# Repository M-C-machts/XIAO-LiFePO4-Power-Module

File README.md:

# XIAO LiFePO4 Module (Charging + 3.3V Regulator)

Small power-management PCB for running an ESP32 (or other 3.3V devices) from a single **LiFePO4** cell.

This board provides:
- **LiFePO4 charging** from ~5V input
- Proper handling of **charge + discharge**
- A **stable 3.3V output**
- **Battery voltage sense** output via a resistor divider (for ADC monitoring)

## Form factor / compatibility

This module matches the **Seeed Studio XIAO** form factor (approx. 21 x 17.5 mm) and is intended to be:
- soldered directly onto a **Seeed Studio XIAO ESP32C3** (castellated-module style), or
- used as a small **daughter board** on a larger PCB.

## Connections

- **Battery**: JST SH connector (LiFePO4 cell)
- **Charge input**: ~5V
- **Output**: regulated 3.3V
- **VBAT_SENSE**: divided battery-voltage output (connect to an ADC pin)

> Pin names / exact pinout depends on the PCB revision. See the schematic/PCB files in this repo.

## Typical use cases

- Battery-powered ESP32 sensor nodes
- Small portable projects using XIAO-sized MCUs
- Projects needing safe LiFePO4 charging + regulated 3.3V

## Notes / safety

- Use only **single-cell LiFePO4** batteries.
- Verify polarity before connecting the battery.
- Charging from ~5V assumes a suitable 5V source (USB, regulated supply, etc.).

## Repo contents

- KiCad project files (schematic + PCB)
- Manufacturing outputs - todo
- BOM / assembly notes - todo

## License

todo

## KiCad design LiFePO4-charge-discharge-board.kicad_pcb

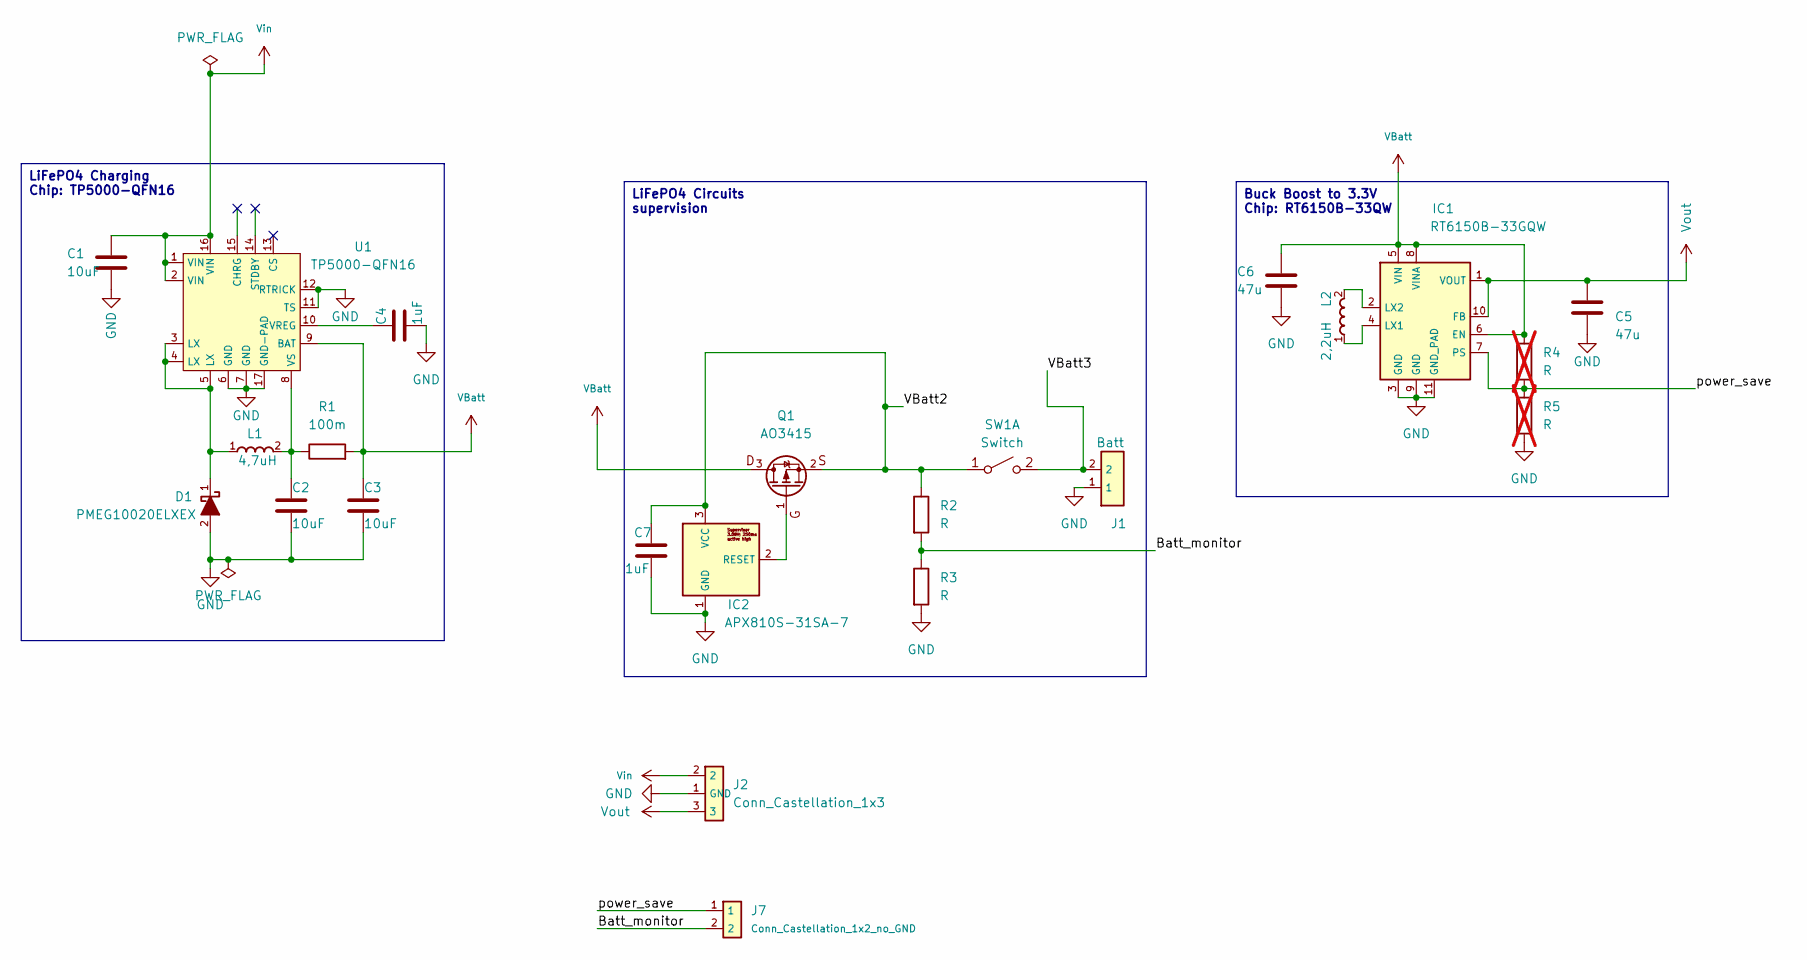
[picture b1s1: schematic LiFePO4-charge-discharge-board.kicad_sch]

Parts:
C1, C2, C3: 10uF; C_0805_2012Metric
C4, C7: 1uF; C_0603_1608Metric
C5, C6: 47u; C_0805_2012Metric
D1: PMEG10020ELXEX; PMEG4010EXEX; Mouser Part Number 771-PMEG10020ELXEX
IC1: RT6150B-33GQW; SON50P250X250X80-11N-D; Mouser Part Number 835-RT6150B-33GQW
IC2: APX810S-31SA-7; SOT-23-3_Marcus; Manufacturer_Part_Number APX810S-31SA-7
J1: Conn_JST-XH_1x2; Mouser Part Number 306-B2B-XH-AMLFSNP
J2: Conn_Castellation_1x3; Conn_Castellated_1x3_GND_moved
J7: Conn_Castellation_1x2_no_GND; Conn_Castellated_1x2_no_GND
L1: 4,7uH; INDC3225X120N
L2: 2,2uH; INDC3225X120N
Q1: AO3415; SOT-23-3_Marcus; Manufacturer_Part_Number AO3415
R1: 100m; R_1206_3216Metric
R2, R3: R; R_0603_1608Metric
R4, R5: R; R_0603_1608Metric; not fitted
SW1: Switch; Conn_Mechc.-solder-pad_1x2
U1: TP5000-QFN16

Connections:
/Batt_monitor: J7.2, R2.2, R3.1
/VBatt2: C7.1, IC2.3 (VCC), Q1.2 (S), R2.1, SW1.1 (A)
/VBatt3: J1.2, SW1.2 (B)
/power_save: IC1.7 (PS), J7.1, R4.2, R5.1
GND: C1.2, C2.2, C3.2, C4.2, C5.2, C6.2, C7.2, D1.2, IC1.3 (GND), IC1.9 (GND), IC1.11 (GND_PAD), IC2.1 (GND), J1.1, J2.1 (GND), R3.2, R5.2, U1.6 (GND), U1.7 (GND), U1.11 (TS), U1.12 (RTRICK), U1.17 (GND-PAD)
unnamed: D1.1, L1.1, U1.3 (LX), U1.4 (LX), U1.5 (LX)
unnamed: IC1.4 (LX1), L2.1
unnamed: IC1.2 (LX2), L2.2
unnamed: IC2.2 (RESET), Q1.1 (G)
unnamed: C4.1, U1.10 (VREG)
unnamed: C2.1, L1.2, R1.1, U1.8 (VS)
VBatt: C3.1, C6.1, IC1.5 (VIN), IC1.6 (EN), IC1.8 (VINA), Q1.3 (D), R1.2, R4.1, U1.9 (BAT)
Vin: C1.1, J2.2, U1.1 (VIN), U1.2 (VIN), U1.16 (VIN)
Vout: C5.1, IC1.1 (VOUT), IC1.10 (FB), J2.3

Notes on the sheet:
Buck Boost to 3.3V Chip: RT6150B-33QW
LiFePO4 Circuits supervision
LiFePO4 Charging Chip: TP5000-QFN16

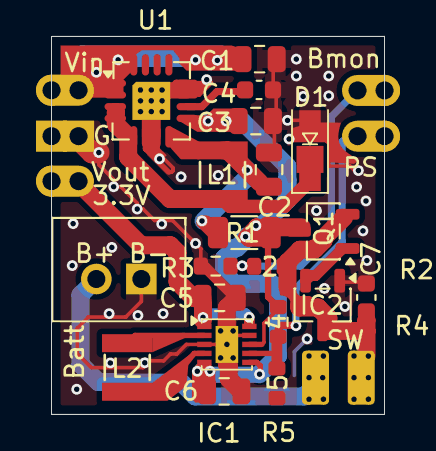
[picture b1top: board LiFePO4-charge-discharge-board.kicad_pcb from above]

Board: 2 copper layers, 18.5 x 21.0 mm, 23 parts (0 on the bottom side), 14 nets.

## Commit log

2026-02-04 Add new project
2026-02-05 Add Working charge section
2026-02-08 rewire circuit
2026-02-19 Finish version V1.0
2026-02-21 Reorganize repo
2026-02-21 Save
